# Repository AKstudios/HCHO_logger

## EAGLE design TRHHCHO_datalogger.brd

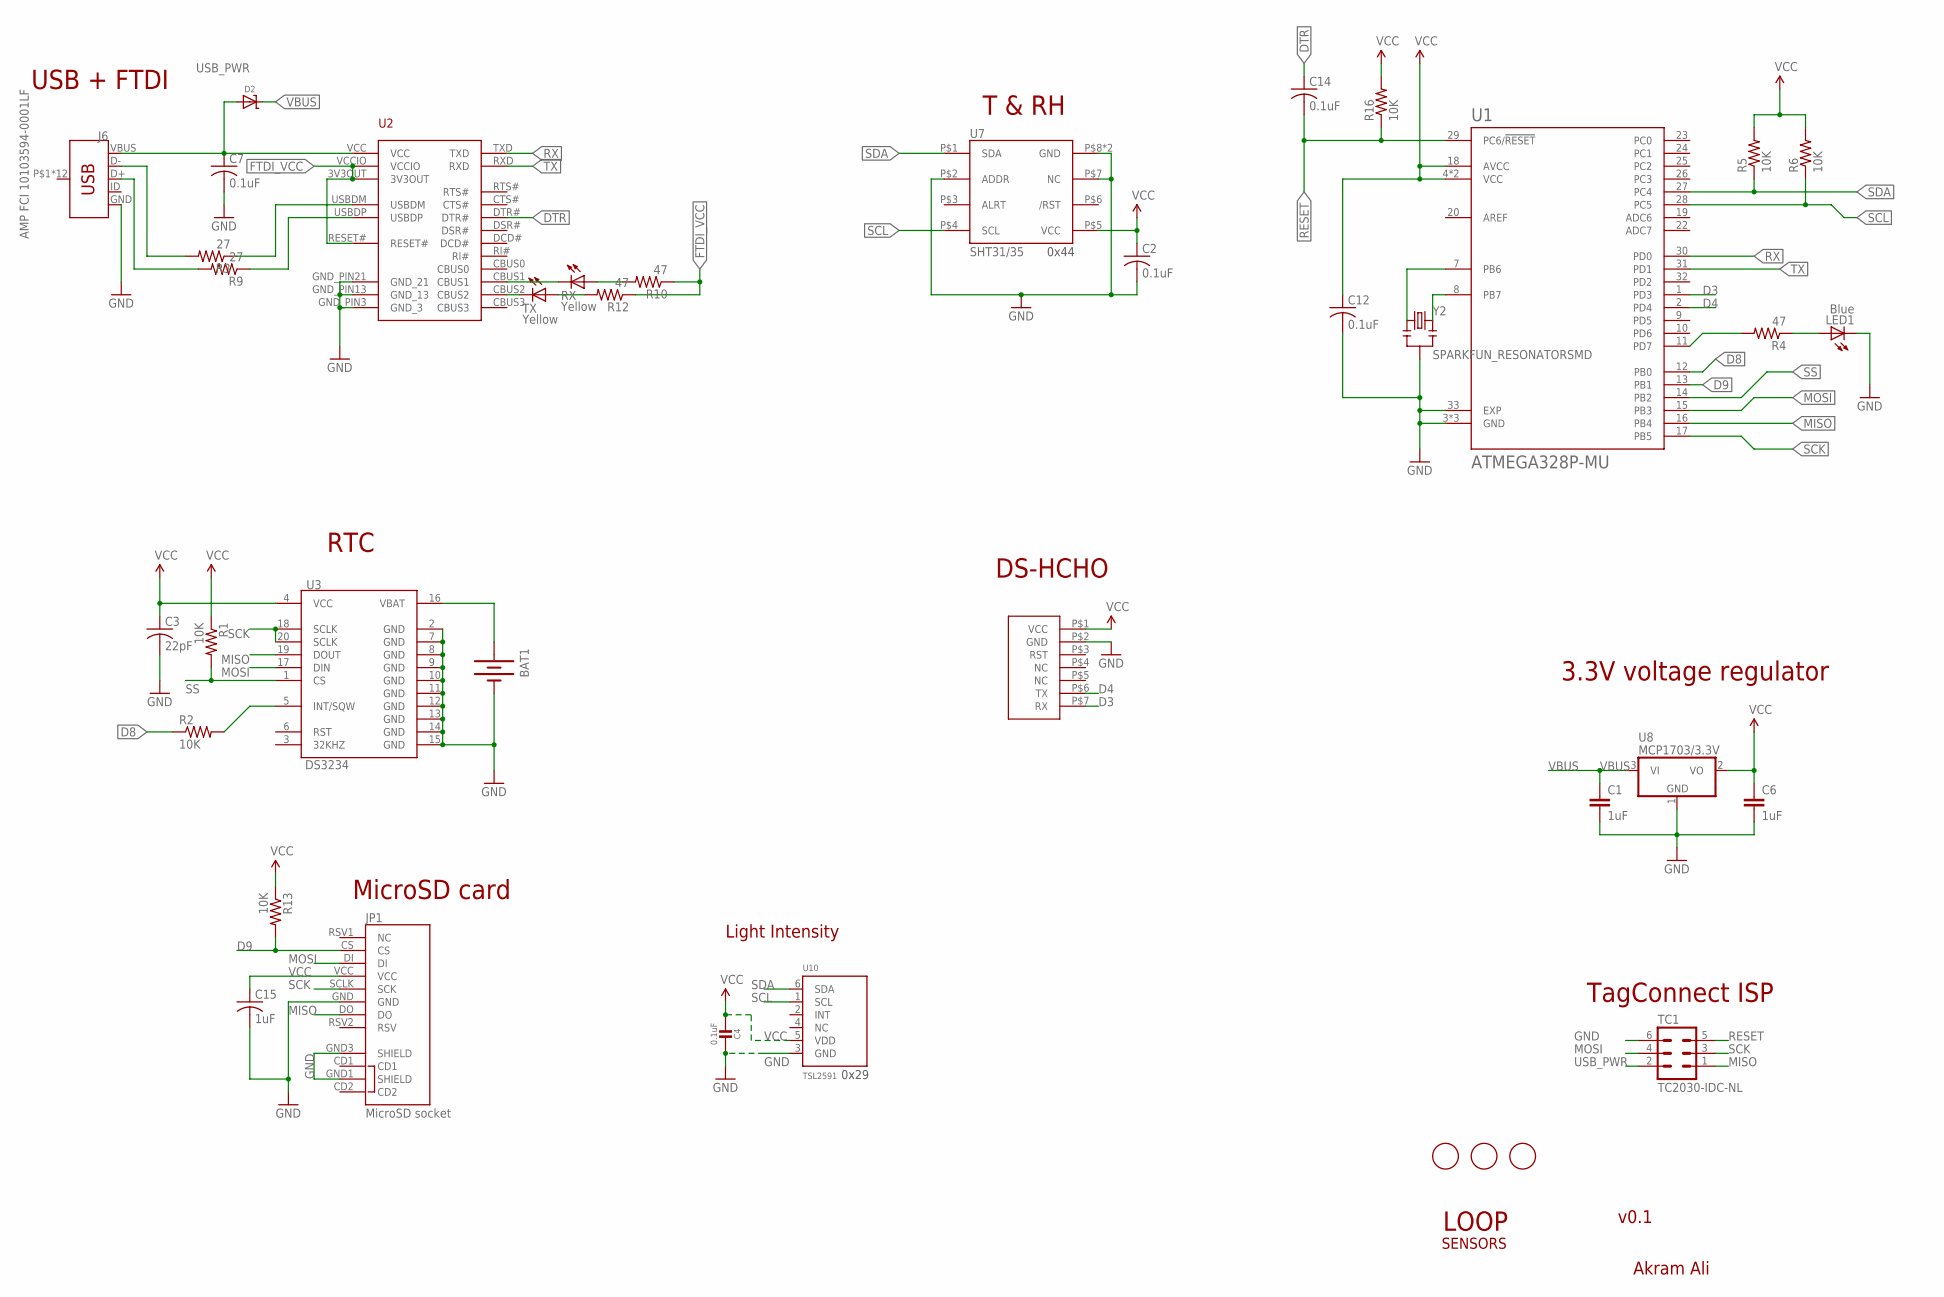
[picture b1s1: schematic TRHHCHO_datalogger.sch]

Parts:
BAT1: BATTERY12MM; BATTCON_12MM; MPN 3000
C1, C6: 1uF; 0805; MPN CC0805KKX7R7BB105
C2, C7, C12, C14: 0.1uF; C0402
C3: 22pF; C0402
C4: 0.1uF; MICROBUILDER__0402MP; MPN GRM155R71C104KA88J
C15: 1uF; C0402
D2: MICROBUILDER_DIODE-SCHOTTKYSOD-123; MICROBUILDER_SOD-123
J6: AMP FCI 10103594-0001LF; USB-MICROB-PTH
JP1: MicroSD socket; MICRO-SD-SOCKET-PP
LED1: Blue; CHIPLED_0805; MPN 150080BS75000
R1, R2, R5, R6, R13, R16: 10K; R0402
R3, R9: 27; R0402
R4, R10, R12: 47; R0402
RX: Yellow; CHIPLED_0805; MPN LG R971-KN-1
TC1: TC2030-IDC-NL
TX: Yellow; CHIPLED_0805; MPN LH R974-LP-1
U1: ATMEGA328P-MU; QFN50P500X500X100-33N
U2: FT231XQ-R; FTDI_FT231XQ-R_PACKAGE; MPN FT231XQ-R
U3: DS3234; MPN DS3234S#
U7: SHT31/35; SHT3X; MPN SHT31-DIS-B
U8: MCP1703/3.3V; SOT23; MPN MCP1703T-2502E/CB
U10: TSL2591; DFN6_TAOS; MPN TSL25911FN
U$1, U$2, U$3: FIDUCIAL; FIDUCIAL_1MM
U$5: DS_HCHO
Y2: SPARKFUN_RESONATORSMD; SPARKFUN_RESONATOR-SMD

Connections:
D3: U1.1 (PD3), U$5.P$7 (RX)
D4: U1.2 (PD4), U$5.P$6 (TX)
D8: R2.1, U1.12 (PB0)
D9: JP1.CS, R13.2, U1.13 (PB1)
DTR: C14.1, U2.DTR#
FTDI_VCC: R10.1, R12.1, U2.3V3OUT, U2.RESET#, U2.VCCIO
GND: BAT1.GND (-), C1.2, C2.2, C3.2, C4.1, C6.2, C7.2, C12.2, C15.2, J6.GND, JP1.GND, JP1.GND1 (SHIELD), JP1.GND3 (SHIELD), LED1.C, TC1.6, U1.3 (GND), U1.5 (GND), U1.21 (GND), U1.33 (EXP), U2.GND_PIN3 (GND_3), U2.GND_PIN13 (GND_13), U2.GND_PIN21 (GND_21), U3.2 (GND), U3.7 (GND), U3.8 (GND), U3.9 (GND), U3.10 (GND), U3.11 (GND), U3.12 (GND), U3.13 (GND), U3.14 (GND), U3.15 (GND), U7.P$2 (ADDR), U7.P$7 (NC), U7.P$8 (GND), U7.PAD (GND), U8.1 (GND), U10.3 (GND), U$5.P$2 (GND), Y2.2
MISO: JP1.DO, TC1.1, U1.16 (PB4), U3.19 (DOUT)
MOSI: JP1.DI, TC1.4, U1.15 (PB3), U3.17 (DIN)
unnamed: R4.2, U1.11 (PD7)
unnamed: R2.2, U3.5 (INT/SQW)
unnamed: LED1.A, R4.1
unnamed: U1.8 (PB7), Y2.3
unnamed: U1.7 (PB6), Y2.1
unnamed: BAT1.PWR@1 (+), U3.16 (VBAT)
unnamed: RX.C, U2.CBUS1
unnamed: TX.C, U2.CBUS2
unnamed: R3.1, U2.USBDM
unnamed: R9.1, U2.USBDP
unnamed: R10.2, RX.A
unnamed: R12.2, TX.A
unnamed: J6.D-, R3.2
unnamed: J6.D+, R9.2
RESET: C14.2, R16.1, TC1.5, U1.29 (PC6/!RESET)
RX: U1.30 (PD0), U2.TXD
SCK: JP1.SCLK (SCK), TC1.3, U1.17 (PB5), U3.18 (SCLK), U3.20 (SCLK)
SCL: R6.1, U1.28 (PC5), U7.P$4 (SCL), U10.1 (SCL)
SDA: R5.1, U1.27 (PC4), U7.P$1 (SDA), U10.6 (SDA)
SS: R1.2, U1.14 (PB2), U3.1 (CS)
TX: U1.31 (PD1), U2.RXD
USB_PWR: C7.1, D2.A, J6.VBUS, TC1.2, U2.VCC
VBUS: C1.1, D2.C, U8.3 (VI)
VCC: C2.1, C3.1, C4.2, C6.1, C12.1, C15.1, JP1.VCC, R1.1, R5.2, R6.2, R13.1, R16.2, U1.4 (VCC), U1.6 (VCC), U1.18 (AVCC), U3.4 (VCC), U7.P$5 (VCC), U8.2 (VO), U10.5 (VDD), U$5.P$1 (VCC)

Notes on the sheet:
T & RH
3.3V voltage regulator
LOOP
Akram Ali
USB + FTDI
0x44
MicroSD card
RTC
v0.1
SENSORS
TagConnect ISP
DS-HCHO
Light Intensity
0x29

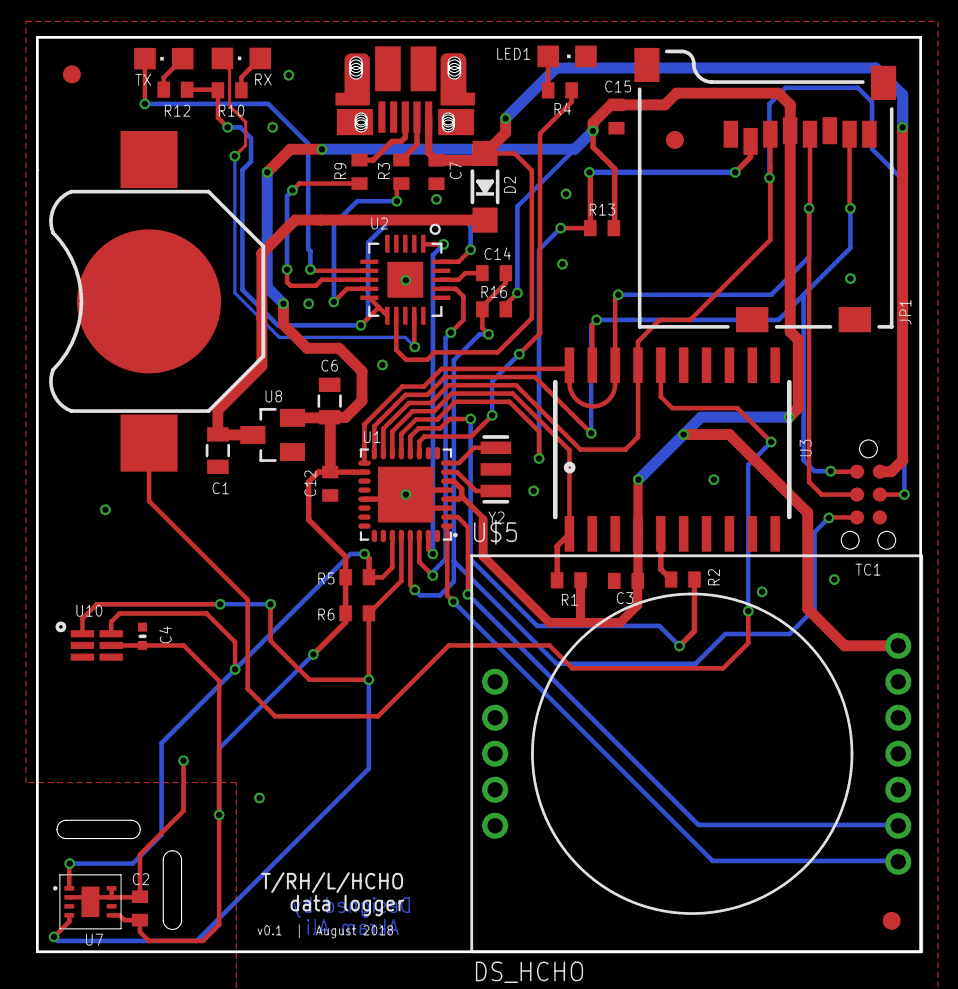
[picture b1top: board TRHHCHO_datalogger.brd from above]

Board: 2 copper layers, 49.1 x 50.8 mm, 39 parts (0 on the bottom side), 33 nets.

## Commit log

2018-08-14 Updated footprint of HCHO sensor
    - Now using proper dimensions given by manufacturer
    - Small trace adjustments
2018-08-14 minor component placement update
    - moved some traces and components so they dont' overlap with silkscreen and keepout
    - ERC/DRC
2018-09-06 Firmware updated
    - Now using NeoSWserial library for software serial (more reliable than software serial)
    - Removed ISR declaration from code (library has it declared)
    - Added code for HCHO sensor
    - Cleaned up code and verified that it works for the board
2018-11-21 Added supporting docs

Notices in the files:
parts and their libraries:
SparkFun-Connectors: Licensing: Creative Commons ShareAlike 4.0 International - https://creativecommons.org/licenses/by-sa/4.0
